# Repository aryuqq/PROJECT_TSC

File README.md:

# InkTime v6 - Advanced Open Source Smartwatch

InkTime v6 este un smartwatch open-source de inalta performanta, axat pe eficienta energetica extrema si un factor de forma compact. Aceasta revizie hardware aduce imbunatatiri majore pe partea de management al energiei, feedback haptic avansat si generarea tensiunilor pentru display direct pe placa de baza.

Acest repository contine fisierele de design hardware (Schematice, PCB layout, BOM) pentru faza **EVT (Engineering Validation Test)** a versiunii 6.

## 1. Diagrama Bloc a Sistemului

```mermaid
graph TD
    %% Power Management
    USB[Conector USB-C / ESD] -->|5V| CHG[IC Incarcare BQ25180]
    CHG --> BATT[Acumulator LiPo 3.7V]
    BATT --> FG[Fuel Gauge MAX17048]
    BATT --> DCDC[Buck-Boost RT6160]
    
    %% Core Power
    DCDC -.->|3.3V Stabilizat| MCU[SoC nRF52840]
    DCDC -.->|3.3V| PERIPH[Periferice]
    
    %% Core & Connectivity
    MCU <-->|I2C| FG
    
    %% Interfaces & Peripherals
    MCU <-->|SPI + Control| EINK[Display E-Paper 1.54]
    MCU -->|PWM/Control| EINK_DRV[Circuit E-Paper Drive On-Board]
    MCU <-->|I2C + INT| IMU[Accelerometru BMA423]
    MCU <-->|I2C + EN| HAPTIC[Driver Haptic DRV2605]
    HAPTIC --> VIB[Motor LRA/ERM]
    MCU -->|GPIO| BTN[3x Butoane Navigare]
```

## 2. Bill Of Materials (BOM)

Tabelul de mai jos contine circuitele integrate (IC-urile) principale folosite in designul placii. Lista completa se gaseste in fisierul .csv din folderul Manufacturing.
| Componenta | Rol in sistem | JLC Part # | Link Datasheet |
| :--- | :--- | :--- | :--- |
| **nRF52840-QIAA** | Microcontroller principal (BLE, Cortex-M4F) | C206001 | [Datasheet nRF52840](https://infocenter.nordicsemi.com/pdf/nRF52840_PS_v1.7.pdf) |
| **BQ25180YBGR** | IC Incarcare liniara avansata (Ultra-Low Iq) | N/A | [Datasheet BQ25180](https://www.ti.com/lit/ds/symlink/bq25180.pdf) |
| **RT6160AWSC** | Regulator DC/DC Buck-Boost 3.3V | C2836254 | [Datasheet RT6160](https://www.richtek.com/assets/product_file/RT6160A/DS6160A-02.pdf) |
| **MAX17048G+T10** | Fuel Gauge (Monitorizare Baterie prin I2C) | C113374 | [Datasheet MAX17048](https://www.analog.com/media/en/technical-documentation/data-sheets/MAX17048-MAX17049.pdf) |
| **BMA423** | Accelerometru Ultra-Low Power (Pedometer HW) | C283084 | [Datasheet BMA423](https://www.bosch-sensortec.com/media/boschsensortec/downloads/datasheets/bst-bma423-ds004.pdf) |
| **DRV2605YZFR** | Driver Haptic I2C (Generare vibratii complexe) | C63435 | [Datasheet DRV2605](https://www.ti.com/lit/ds/symlink/drv2605.pdf) |
| **USBLC6-2SC6Y** | Protectie ESD pe liniile de date si alimentare USB-C | C7519 | [Datasheet USBLC6](https://www.st.com/resource/en/datasheet/usblc6-2.pdf) |

## 3. Descrierea Functionalitatii Hardware
### Procesare si Conectivitate:

Inima ceasului InkTime este SoC-ul Nordic nRF52840. A fost ales datorita suportului nativ pentru Bluetooth 5.0 (BLE), esential pentru sincronizarea notificarilor cu telefonul mobil. Arhitectura ARM Cortex-M4F permite procesarea eficienta a algoritmilor senzorilor.
Managementul Consumului de Energie (Power Tree):

Fiind un dispozitiv wearable, constrangerile de baterie sunt critice. Sistemul energetic a fost complet reproiectat in v6.

Sistemul este alimentat de o baterie LiPo de mici dimensiuni (ex. 500mAh). Monitorizarea starii de incarcare (SoC) se face precis si fara consum mare de curent prin cipul MAX17048.

Incarcarea se face la 5V printr-un circuit BQ25180, un cip de top care permite controlul precis al pragurilor de incarcare.

Pentru a asigura tensiunea de 3.3V am folosit un convertor Buck-Boost RT6160 in loc de un LDO simplu. Acesta mentine 3.3V perfect stabil chiar si cand tensiunea bateriei scade, extragand maximum de energie din acumulator inainte de oprire.

### Periferice si Interfete:

Display-ul E-Ink: Comunica prin protocol SPI. Fata de versiunile anterioare, placa include propriul circuit de generare a tensiunilor inalte (E-Paper Drive On-Board cu inductor si mosfet), ceea ce reduce grosimea totala. Consuma 0mA pentru a mentine imaginea afisata.

Senzorii (IMU, Haptic, Fuel Gauge): Comunicatia se realizeaza pe o magistrala I2C partajata. BMA423 are un mod special de "step counter" hardware care poate trezi microcontroller-ul din sleep doar cand utilizatorul face un pas. Driver-ul DRV2605 ofera feedback haptic premium, descarcand procesorul de generarea semnalelor PWM.

## 4. Alocarea Pinilor nRF52840

Microcontroller-ul nRF52840 permite maparea flexibila a pinilor (orice functie digitala pe orice pin), lucru care a facilitat o rutare curata pe PCB.

| Pin nRF52840 | Nume Net / Functie | Justificare / Detalii |
| :--- | :--- | :--- |
| **P0.26 / P0.27** | `SDA/2.4C`, `SCL/2.4C` | Magistrala I2C principala (IMU, Haptic, Fuel Gauge, Charger). Contine rezistente de pull-up. |
| **P0.08 / P1.09** | `IMU_INT1`, `IMU_INT2` | Pini de intrerupere hardware. BMA423 trimite semnale aici pentru a trezi SoC-ul cand detecteaza miscare. |
| **P0.12** | `HAPTIC_EN` | Pin configurat ca iesire pentru a activa/dezactiva driver-ul de vibratii DRV2605. |
| **P0.04** | `EPD_CS` | Chip Select pentru activarea magistralei SPI a display-ului E-Paper. |
| **P0.13 - P0.15** | `MOSI`, `MISO`, `SCK` | Magistrala SPI hardware (rutata direct catre conectorul FPC de 24 pini). |
| **Diverse** | `SW_UP`, `SW_ENT`, `SW_DN` | Pini conectati la butoanele laterale, configurati cu retele RC (Hardware Debouncing) pentru o citire curata. |

## 5. Design Log & Integrare Mecanica
### Constructia PCB-ului:

Layout-ul este extrem de dens, folosind componente in capsule miniaturale (BGA si QFN). Rutarea respecta zona de "Keepout" a antenei de 2.4GHz, asigurand o bataie maxima a semnalului Bluetooth.
Interfete Fizice:

Conectorul USB Type-C este utilizat exclusiv pentru incarcare (5V) si a fost ranforsat mecanic. Debug-ul se face prin footprint-ul SWD standardizat (Tag-Connect TC2030).

## 6. Calcule Detaliate de Consum de Energie (Power Budget)

Dispozitivul este proiectat sa functioneze cu un acumulator LiPo de 500 mAh.
### Consum in Mod Sleep (Standby / System OFF)

    * nRF52840 (Sleep): ~1.5 uA

    * BMA423 (Low Power): ~2.0 uA

    * MAX17048 (Hibernate): ~0.5 uA

    * BQ25180 (Battery Discharge): ~10.0 uA

    * RT6160 (Quiescent): ~1.0 uA

    * Total Consum Sleep: ~15.0 uA (0.015 mA)

### Consum in Mod Activ (Actualizare Ecran / Bluetooth)

    * nRF52840 (CPU + TX RF): ~14.0 mA

    * E-Paper Drive (in timpul refresh-ului): ~8.0 mA

    * Total Consum Activ (varf): ~22.0 mA

### Estimarea Autonomiei

Presupunand un ciclu de utilizare cu 50 de treziri pe zi si o medie calculata de 0.15 mA consum hibrid:

500 mAh / 0.15 mA = 3333 ore = Aproximativ 138 de zile (peste 4 luni) teoretice cu o singura incarcare.

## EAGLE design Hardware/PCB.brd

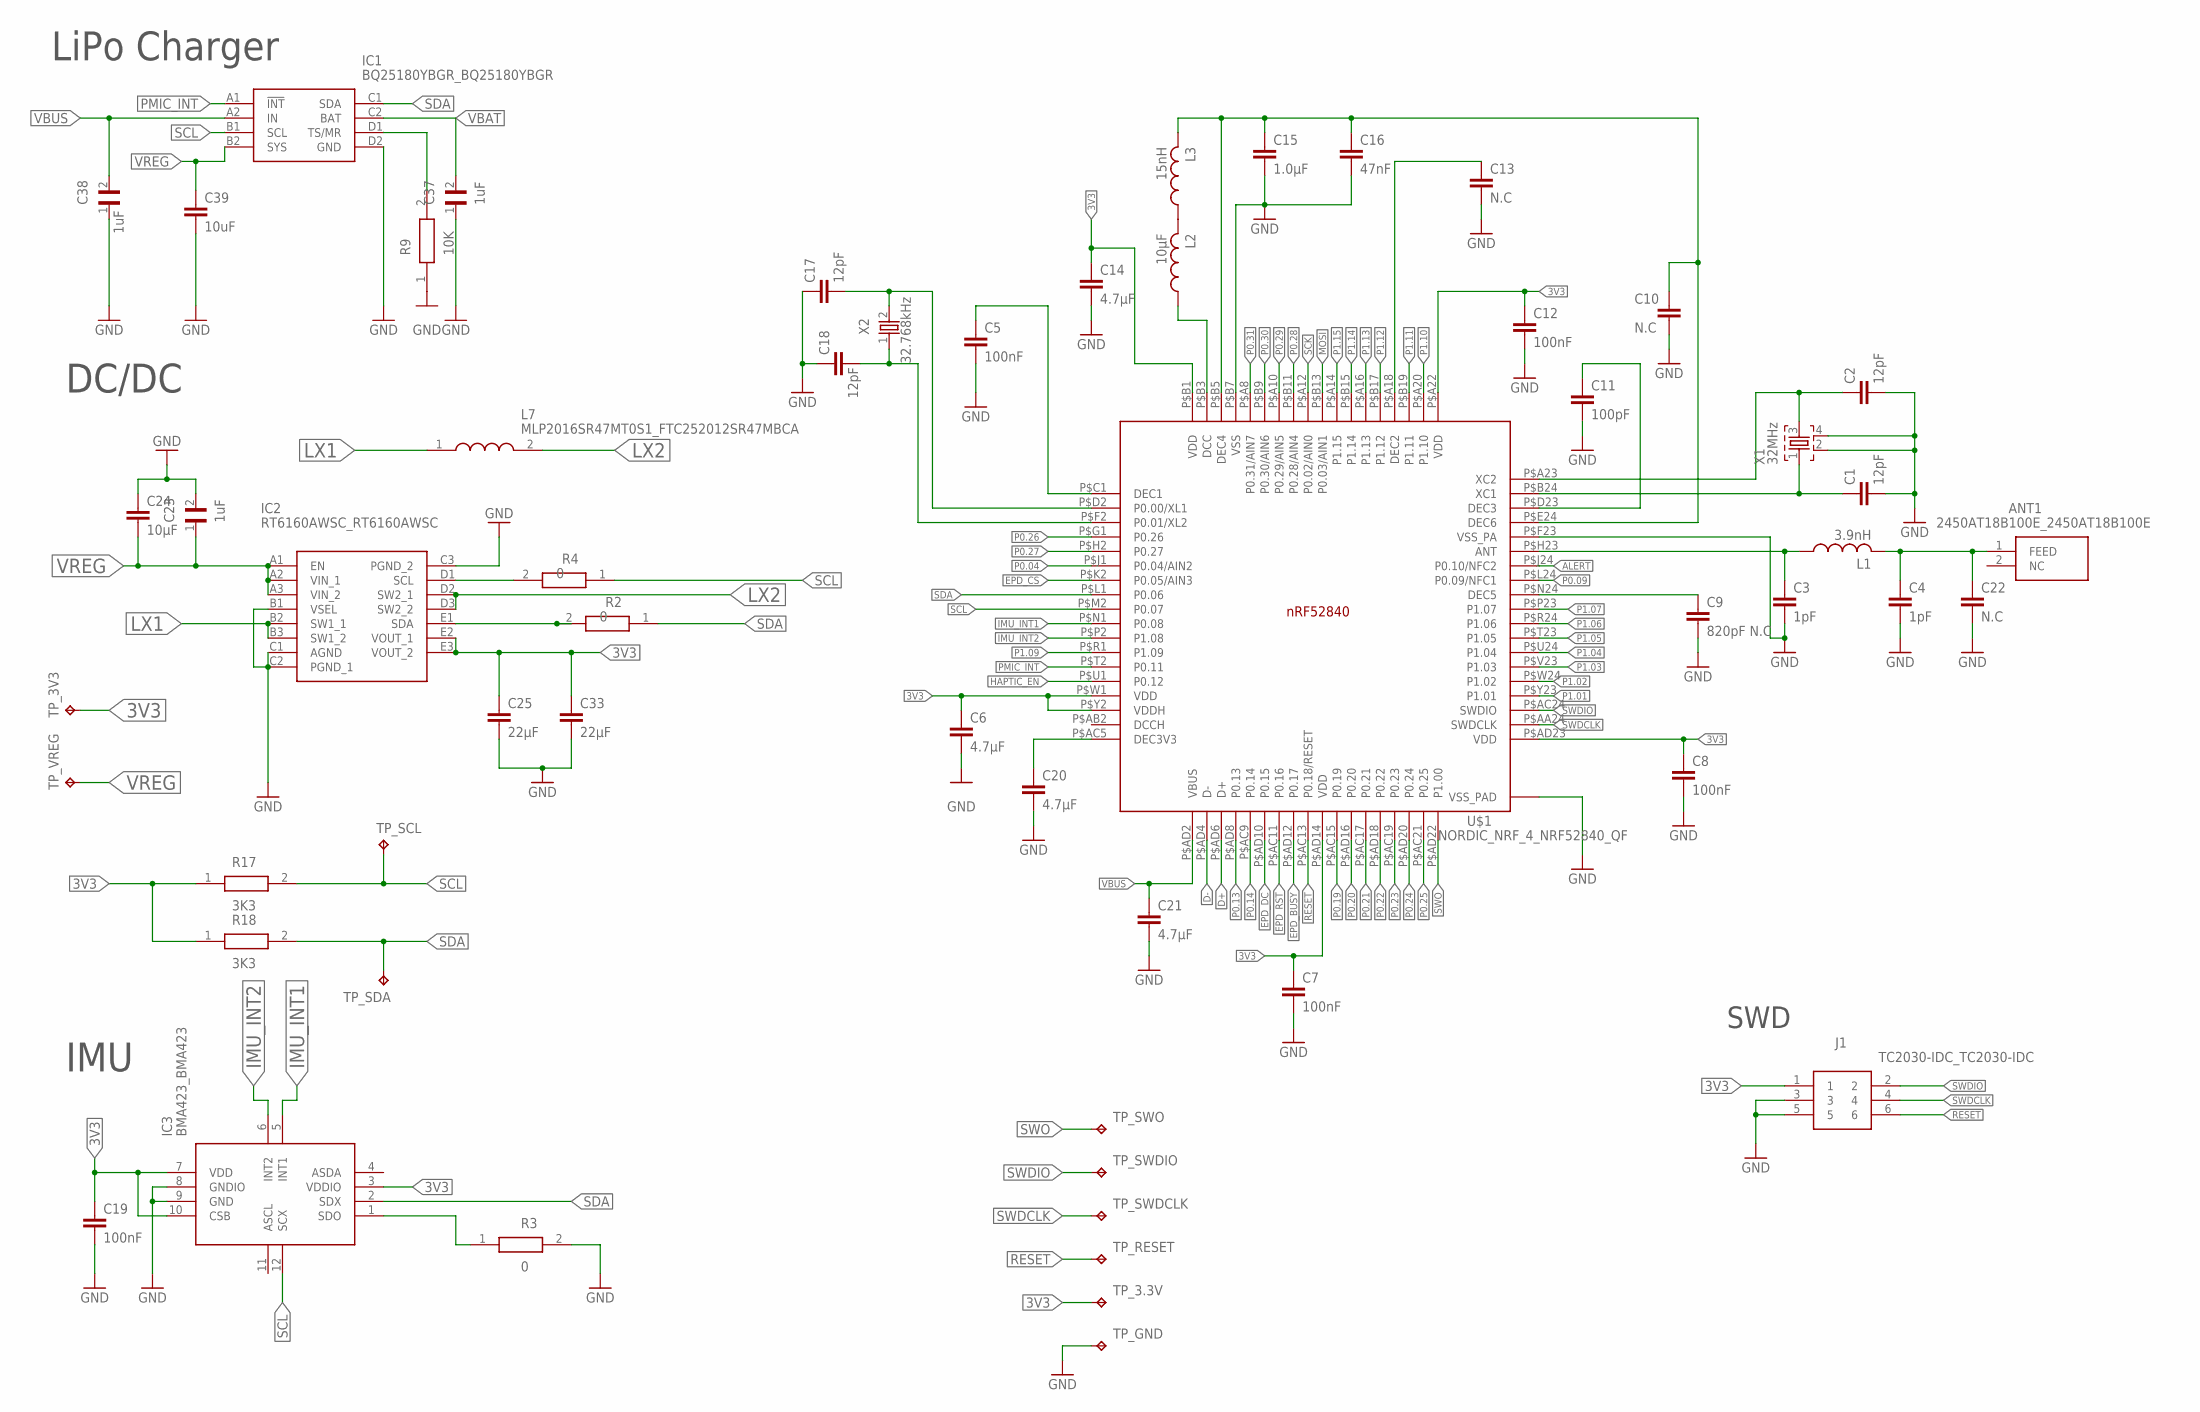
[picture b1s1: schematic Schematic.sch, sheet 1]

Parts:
ANT1: 2450AT18B100E_2450AT18B100E; 2450AT18B100E_ANTC3216X140N
C1, C2, C17, C18: 12pF; NORDIC_NRF_3_RESC0201_L
C3, C4: 1pF; NORDIC_NRF_3_RESC0201_L
C5, C7, C8, C12, C19: 100nF; NORDIC_NRF_3_RESC0201_L
C6, C14, C20, C21: 4.7µF; PERFECT_0402_0402
C9: 820pF N.C; NORDIC_NRF_3_RESC0201_L
C10: N.C; PERFECT_0402_0402
C11: 100pF; NORDIC_NRF_3_RESC0201_L
C13, C22: N.C; NORDIC_NRF_3_RESC0201_L
C15: 1.0µF; PERFECT_0402_0402
C16: 47nF; NORDIC_NRF_3_RESC0201_L
C23, C37, C38: 1uF; GRM011R60J152KE01L_2_CAPC0201X13N
C24: 10µF; PERFECT_0402_0402
C25, C33: 22µF; PERFECT_0402_0402
C39: 10uF; PERFECT_0402_0402
IC1: BQ25180YBGR_BQ25180YBGR; BQ25180YBGR_BGA8C40P2X4_100X155X50
IC2: RT6160AWSC_RT6160AWSC; RT6160AWSC_BGA15C40P3X5_140X230X60
IC3: BMA423_BMA423
J1: TC2030-IDC_TC2030-IDC; TC2030-IDC_TC2030IDC
L1: 3.9nH; NORDIC_NRF_2_RESC0402_L
L2: 10µF; NORDIC_NRF_2_RESC0402_L
L3: 15nH; NORDIC_NRF_2_RESC0402_L
L7: MLP2016SR47MT0S1_FTC252012SR47MBCA; MLP2016SR47MT0S1_INDC2016X100N
R2, R3, R4: 0; CPF0201D7K68C1_0201
R9: 10K; CPF0201D7K68C1_0201
R17, R18: 3K3; ERA-1AEB3401C_0201
TP_3.3V, TP_3V3: HECTOR_WATCH_1_TPTP20R; HECTOR_WATCH_1_TP20R
TP_GND: HECTOR_WATCH_1_TPTP20R; HECTOR_WATCH_1_TP20R
TP_RESET: HECTOR_WATCH_1_TPTP20R; HECTOR_WATCH_1_TP20R
TP_SCL: HECTOR_WATCH_1_TPTP20R; HECTOR_WATCH_1_TP20R
TP_SDA: HECTOR_WATCH_1_TPTP20R; HECTOR_WATCH_1_TP20R
TP_SWDCLK: HECTOR_WATCH_1_TPTP20R; HECTOR_WATCH_1_TP20R
TP_SWDIO: HECTOR_WATCH_1_TPTP20R; HECTOR_WATCH_1_TP20R
TP_SWO: HECTOR_WATCH_1_TPTP20R; HECTOR_WATCH_1_TP20R
TP_VREG: HECTOR_WATCH_1_TPTP20R; HECTOR_WATCH_1_TP20R
U$1: NORDIC_NRF_4_NRF52840_QF; NORDIC_NRF_4_AQFN50P700X700X85_HS-74N
X1: 32MHz; NORDIC_NRF_BT-XTAL_2016_N
X2: 32.768kHz; NORDIC_NRF_1_XTAL_3215_N

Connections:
3V3: C6.1, C7.1, C8.1, C12.1, C14.1, C19.1, C25.1, C33.1, IC2.E2 (VOUT_1), IC2.E3 (VOUT_2), IC3.3 (VDDIO), IC3.7 (VDD), IC3.10 (CSB), J1.1, R17.1, R18.1, TP_3.3V.TP, TP_3V3.TP, U$1.P$A22 (VDD), U$1.P$AD14 (VDD), U$1.P$AD23 (VDD), U$1.P$B1 (VDD), U$1.P$W1 (VDD), U$1.P$Y2 (VDDH); also elsewhere on the board
ALERT: U$1.P$J24 (P0.10/NFC2); also elsewhere on the board
D+: U$1.P$AD6 (D+); also elsewhere on the board
D-: U$1.P$AD4 (D-); also elsewhere on the board
EPD_BUSY: U$1.P$AD12 (P0.17); also elsewhere on the board
EPD_CS: U$1.P$K2 (P0.05/AIN3); also elsewhere on the board
EPD_DC: U$1.P$AD10 (P0.15); also elsewhere on the board
EPD_RST: U$1.P$AC11 (P0.16); also elsewhere on the board
GND: C1.2, C2.2, C3.2, C4.2, C5.2, C6.2, C7.2, C8.2, C9.2, C10.2, C11.2, C12.2, C13.2, C14.2, C15.2, C16.2, C17.1, C18.1, C19.2, C20.2, C21.2, C22.2, C23.2, C24.1, C25.2, C33.2, C37.1, C38.1, C39.2, IC1.D2 (GND), IC2.B1 (VSEL), IC2.C1 (AGND), IC2.C2 (PGND_1), IC2.C3 (PGND_2), IC3.8 (GNDIO), IC3.9 (GND), J1.3, J1.5, R3.2, R9.1, TP_GND.TP, U$1.P$74 (VSS_PAD), U$1.P$75 (VSS_PAD), U$1.P$76 (VSS_PAD), U$1.P$77 (VSS_PAD), U$1.P$78 (VSS_PAD), U$1.P$79 (VSS_PAD), U$1.P$80 (VSS_PAD), U$1.P$81 (VSS_PAD), U$1.P$82 (VSS_PAD), U$1.P$83 (VSS_PAD), U$1.P$84 (VSS_PAD), U$1.P$85 (VSS_PAD), U$1.P$86 (VSS_PAD), U$1.P$87 (VSS_PAD), U$1.P$88 (VSS_PAD), U$1.P$89 (VSS_PAD), U$1.P$90 (VSS_PAD), U$1.P$B7 (VSS), U$1.P$F23 (VSS_PA), X1.2, X1.4; also elsewhere on the board
HAPTIC_EN: U$1.P$U1 (P0.12); also elsewhere on the board
IMU_INT1: IC3.5 (INT1), U$1.P$N1 (P0.08)
IMU_INT2: IC3.6 (INT2), U$1.P$P2 (P1.08)
LX1: IC2.B2 (SW1_1), IC2.B3 (SW1_2), L7.1
LX2: IC2.D2 (SW2_1), IC2.D3 (SW2_2), L7.2
MOSI: U$1.P$B13 (P0.03/AIN1); also elsewhere on the board
unnamed: L2.2, L3.1
unnamed: L2.1, U$1.P$B3 (DCC)
unnamed: IC1.D1 (TS/MR), R9.2
unnamed: IC3.1 (SDO), R3.1
unnamed: IC2.D1 (SCL), R4.2
unnamed: C10.1, C15.1, C16.1, L3.2, U$1.P$B5 (DEC4), U$1.P$E24 (DEC6)
unnamed: IC2.E1 (SDA), R2.2
unnamed: C13.1, U$1.P$A18 (DEC2)
unnamed: C11.1, U$1.P$D23 (DEC3)
unnamed: C2.1, U$1.P$A23 (XC2), X1.3
unnamed: C1.1, U$1.P$B24 (XC1), X1.1
unnamed: C3.1, L1.1, U$1.P$H23 (ANT)
unnamed: ANT1.1 (FEED), C4.1, C22.1, L1.2
unnamed: C9.1, U$1.P$N24 (DEC5)
unnamed: C20.1, U$1.P$AC5 (DEC3V3)
unnamed: C5.1, U$1.P$C1 (DEC1)
unnamed: C17.2, U$1.P$D2 (P0.00/XL1), X2.2
unnamed: C18.2, U$1.P$F2 (P0.01/XL2), X2.1
P0.04: U$1.P$J1 (P0.04/AIN2)
P0.09: U$1.P$L24 (P0.09/NFC1)
P0.13: U$1.P$AD8 (P0.13); also elsewhere on the board
P0.14: U$1.P$AC9 (P0.14); also elsewhere on the board
P0.19: U$1.P$AC15 (P0.19)
P0.20: U$1.P$AD16 (P0.20)
P0.21: U$1.P$AC17 (P0.21)
P0.22: U$1.P$AD18 (P0.22)
P0.23: U$1.P$AC19 (P0.23)
P0.24: U$1.P$AD20 (P0.24)
P0.25: U$1.P$AC21 (P0.25)
P0.26: U$1.P$G1 (P0.26)
P0.27: U$1.P$H2 (P0.27)
P0.28: U$1.P$B11 (P0.28/AIN4)
P0.29: U$1.P$A10 (P0.29/AIN5)
P0.30: U$1.P$B9 (P0.30/AIN6)
P0.31: U$1.P$A8 (P0.31/AIN7)
P1.01: U$1.P$Y23 (P1.01); also elsewhere on the board
P1.02: U$1.P$W24 (P1.02); also elsewhere on the board
P1.03: U$1.P$V23 (P1.03)
P1.04: U$1.P$U24 (P1.04)
P1.05: U$1.P$T23 (P1.05)
P1.06: U$1.P$R24 (P1.06)
P1.07: U$1.P$P23 (P1.07)
P1.09: U$1.P$R1 (P1.09)
P1.10: U$1.P$A20 (P1.10)
P1.11: U$1.P$B19 (P1.11)
P1.12: U$1.P$B17 (P1.12)
P1.13: U$1.P$A16 (P1.13)
P1.14: U$1.P$B15 (P1.14)
P1.15: U$1.P$A14 (P1.15)
PMIC_INT: IC1.A1 (!INT), U$1.P$T2 (P0.11)
RESET: J1.6, TP_RESET.TP, U$1.P$AC13 (P0.18/RESET)
SCK: U$1.P$A12 (P0.02/AIN0); also elsewhere on the board
SCL: IC1.B1 (SCL), IC3.12 (SCX), R4.1, R17.2, TP_SCL.TP, U$1.P$M2 (P0.07); also elsewhere on the board
SDA: IC1.C1 (SDA), IC3.2 (SDX), R2.1, R18.2, TP_SDA.TP, U$1.P$L1 (P0.06); also elsewhere on the board
SWDCLK: J1.4, TP_SWDCLK.TP, U$1.P$AA24 (SWDCLK)
SWDIO: J1.2, TP_SWDIO.TP, U$1.P$AC24 (SWDIO)
SWO: TP_SWO.TP, U$1.P$AD22 (P1.00)
VBAT: C37.2, IC1.C2 (BAT); also elsewhere on the board
VBUS: C21.1, C38.2, IC1.A2 (IN), U$1.P$AD2 (VBUS); also elsewhere on the board
VREG: C23.1, C24.2, C39.1, IC1.B2 (SYS), IC2.A1 (EN), IC2.A2 (VIN_1), IC2.A3 (VIN_2), TP_VREG.TP

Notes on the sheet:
LiPo Charger
DC/DC
IMU
SWD

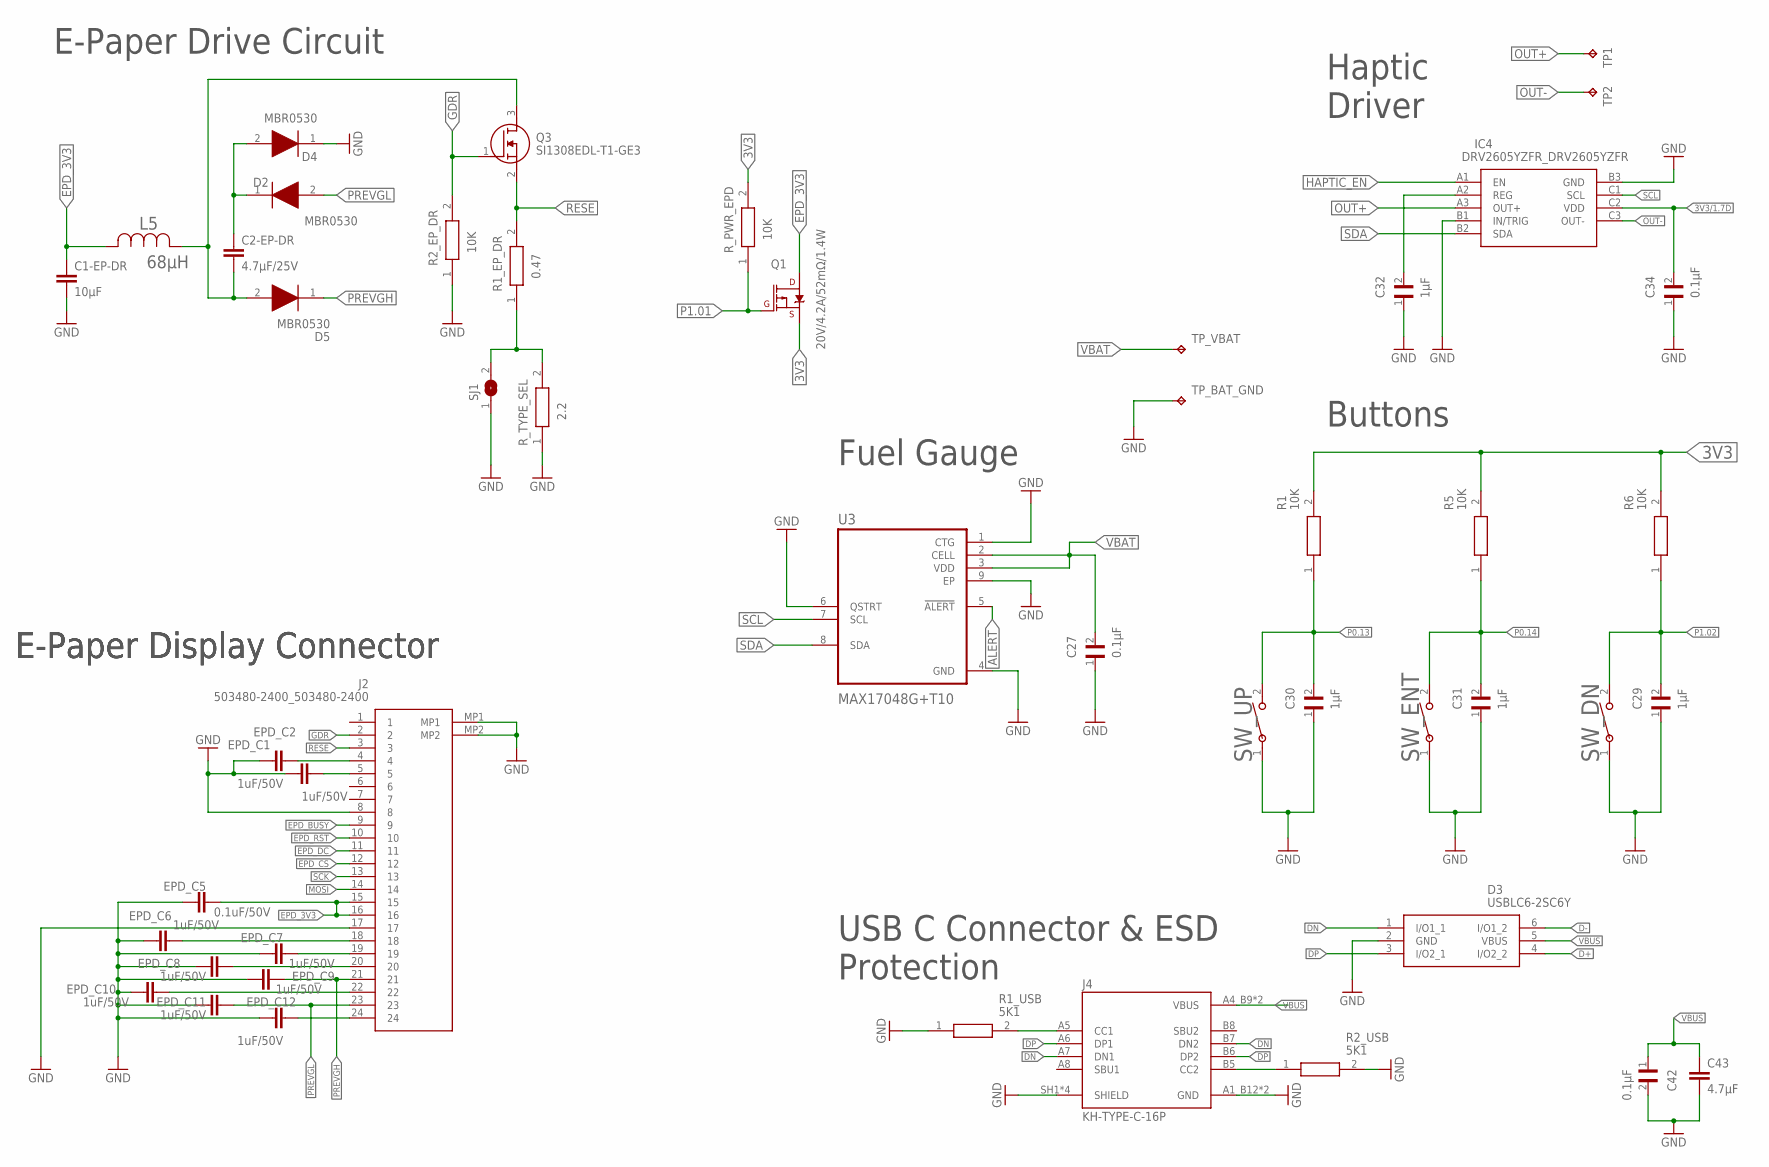
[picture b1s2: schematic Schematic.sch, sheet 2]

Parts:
C1-EP-DR: 10µF; NORDIC_NRF_3_RESC0402_L
C2-EP-DR: 4.7µF/25V; NORDIC_NRF_3_RESC0603_L
C27, C42: 0.1µF; GRM011R60J152KE01L_1_0201
C29, C30, C31, C32: 1µF; GRM011R60J152KE01L_1_0201
C34: 0.1µF; GRM011R60J152KE01L_2_CAPC0201X13N
C43: 4.7µF; PERFECT_0402_0402
D2, D4, D5: MBR0530; ESP32_C6_LIBRARY_5_SOD3716X135N
D3: USBLC6-2SC6Y; ESP32_C6_LIBRARY_3_SOT95P280X145-6N
EPD_C1, EPD_C2, EPD_C6, EPD_C7, EPD_C8, EPD_C9, EPD_C10, EPD_C11, EPD_C12: 1uF/50V; PERFECT_0402_0402
EPD_C5: 0.1uF/50V; NORDIC_NRF_3_RESC0201_L
IC4: DRV2605YZFR_DRV2605YZFR; DRV2605YZFR_BGA9C50P3X3_144X144X62
J2: 503480-2400_503480-2400; 503480-2400_5034802400
J4: KH-TYPE-C-16P; KH-TYPE-C-16P_KINGHELM_KH-TYPE-C-16P
L5: 68µH; ESP32_C6_LIBRARY_2_IND_4828-WE-TPC_WRE
Q1: 20V/4.2A/52mΩ/1.4W; ESP32_C6_LIBRARY_4_ESP32_C6_LIBRARY_4_ESP32_C6_LIBRARY_4_ES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
Q3: SI1308EDL-T1-GE3; ESP32_C6_LIBRARY_6_SOT65P210X110-3N
R1, R2_EP_DR, R5, R6: 10K; CPF0201D7K68C1_0201
R1_EP_DR: 0.47; CPF0201D7K68C1_0201
R1_USB, R2_USB: 5K1; CPF0201D7K68C1_0201
R_PWR_EPD: 10K; CPF0201D7K68C1_0201
R_TYPE_SEL: 2.2; CPF0201D7K68C1_0201
SJ1: ESP32_C6_LIBRARY_7_JUMPER_SJ
SW_DN: 2025-10-22_07-23-44_LIBRARY_EVP-AKE31ASW_EVP-AKE3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; 2025-10-22_07-23-44_LIBRARY_SW_EVP-AKE31A_PAN
SW_ENT: 2025-10-22_07-23-44_LIBRARY_EVP-AKE31ASW_EVP-AKE3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; 2025-10-22_07-23-44_LIBRARY_SW_EVP-AKE31A_PAN
SW_UP: 2025-10-22_07-23-44_LIBRARY_EVP-AKE31ASW_EVP-AKE3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; 2025-10-22_07-23-44_LIBRARY_SW_EVP-AKE31A_PAN
TP1, TP2: HECTOR_WATCH_1_TPTP20R; HECTOR_WATCH_1_TP20R
TP_BAT_GND: HECTOR_WATCH_1_TPTP20R; HECTOR_WATCH_1_TP20R
TP_VBAT: HECTOR_WATCH_1_TPTP20R; HECTOR_WATCH_1_TP20R
U3: MAX17048G+T10; ESP32_C6_LIBRARY_SON50P200X200X80-9N

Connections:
3V3: Q1.2 (S), R1.2, R5.2, R6.2, R_PWR_EPD.2; also elsewhere on the board
3V3/1.7D: C34.2, IC4.C2 (VDD)
ALERT: U3.5 (!ALERT); also elsewhere on the board
D+: D3.4 (I/O2_2); also elsewhere on the board
D-: D3.6 (I/O1_2); also elsewhere on the board
DN: D3.1 (I/O1_1), J4.A7 (DN1), J4.B7 (DN2)
DP: D3.3 (I/O2_1), J4.A6 (DP1), J4.B6 (DP2)
EPD_3V3: C1-EP-DR.1, EPD_C5.2, J2.15, J2.16, L5.2, Q1.3 (D)
EPD_BUSY: J2.9; also elsewhere on the board
EPD_CS: J2.12; also elsewhere on the board
EPD_DC: J2.11; also elsewhere on the board
EPD_RST: J2.10; also elsewhere on the board
GDR: J2.2, Q3.1 (G), R2_EP_DR.2
GND: C1-EP-DR.2, C27.1, C29.1, C30.1, C31.1, C32.1, C34.1, C42.2, C43.2, D3.2 (GND), D4.1 (K), EPD_C1.1, EPD_C2.1, EPD_C5.1, EPD_C6.1, EPD_C7.1, EPD_C8.1, EPD_C9.1, EPD_C10.1, EPD_C11.1, EPD_C12.1, IC4.B1 (IN/TRIG), IC4.B3 (GND), J2.8, J2.17, J2.MP1, J2.MP2, J4.A1_B12 (GND), J4.A12_B1 (GND), J4.SH1 (SHIELD), J4.SH2 (SHIELD), J4.SH3 (SHIELD), J4.SH4 (SHIELD), R1_USB.1, R2_EP_DR.1, R2_USB.2, R_TYPE_SEL.1, SJ1.1, SW_DN.1, SW_ENT.1, SW_UP.1, TP_BAT_GND.TP, U3.1 (CTG), U3.4 (GND), U3.6 (QSTRT), U3.9 (EP); also elsewhere on the board
HAPTIC_EN: IC4.A1 (EN); also elsewhere on the board
MOSI: J2.14; also elsewhere on the board
unnamed: EPD_C1.2, J2.5
unnamed: C2-EP-DR.2, D5.2 (A), L5.1, Q3.3 (D)
unnamed: EPD_C2.2, J2.4
unnamed: C32.2, IC4.A2 (REG)
unnamed: C2-EP-DR.1, D2.1 (K), D4.2 (A)
unnamed: J4.B5 (CC2), R2_USB.1
unnamed: J4.A5 (CC1), R1_USB.2
unnamed: R1_EP_DR.1, R_TYPE_SEL.2, SJ1.2
unnamed: EPD_C6.2, J2.18
unnamed: EPD_C7.2, J2.19
unnamed: EPD_C8.2, J2.20
unnamed: EPD_C10.2, J2.22
unnamed: EPD_C12.2, J2.24
OUT+: IC4.A3 (OUT+), TP1.TP
OUT-: IC4.C3 (OUT-), TP2.TP
P0.13: C30.2, R1.1, SW_UP.2; also elsewhere on the board
P0.14: C31.2, R5.1, SW_ENT.2; also elsewhere on the board
P1.01: Q1.1 (G), R_PWR_EPD.1; also elsewhere on the board
P1.02: C29.2, R6.1, SW_DN.2; also elsewhere on the board
PREVGH: D5.1 (K), EPD_C9.2, J2.21
PREVGL: D2.2 (A), EPD_C11.2, J2.23
RESE: J2.3, Q3.2 (S), R1_EP_DR.2
SCK: J2.13; also elsewhere on the board
SCL: IC4.C1 (SCL), U3.7 (SCL); also elsewhere on the board
SDA: IC4.B2 (SDA), U3.8 (SDA); also elsewhere on the board
VBAT: C27.2, TP_VBAT.TP, U3.2 (CELL), U3.3 (VDD); also elsewhere on the board
VBUS: C42.1, C43.1, D3.5 (VBUS), J4.A4_B9 (VBUS), J4.A9_B4 (VBUS); also elsewhere on the board

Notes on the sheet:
Haptic Driver
Fuel Gauge
Buttons
USB C Connector & ESD Protection
E-Paper Display Connector
E-Paper Drive Circuit

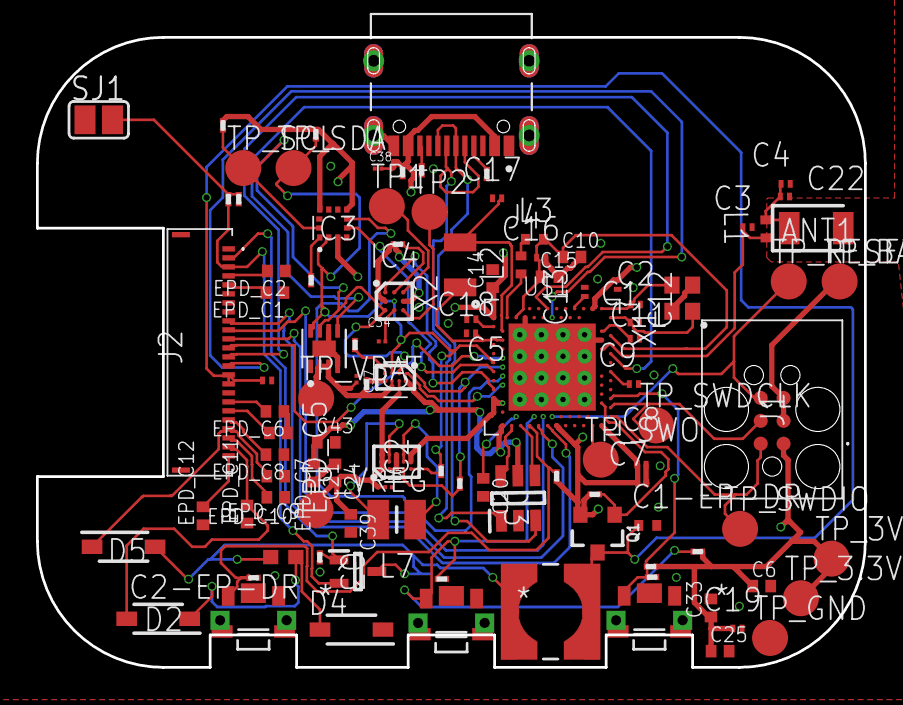
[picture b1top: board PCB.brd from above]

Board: 4 copper layers, 46.0 x 35.0 mm, 105 parts (0 on the bottom side), 71 nets.

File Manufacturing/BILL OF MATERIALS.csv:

Reference Designators;Quantity;Description;Package;Value;Manufacturer;Manufacturer Part Number;Vendor;Vendor Part Number;Top/Bottom;
;1;PCB Board;Board;;;;;;;
ANT1;1;Antennas 2.45GHz ANTENNA;2450AT18B100E_ANTC3216X140N;2450AT18B100E_2450AT18B100E;;;;;Top;
C1, C2, C17, C18;4;Generic chip capacitor;NORDIC_NRF_3_RESC0201_L;12pF;;;;;Top;
C1-EP-DR;1;Generic chip capacitor;NORDIC_NRF_3_RESC0402_L;10µF;;;;;Top;
C2-EP-DR;1;Generic chip capacitor;NORDIC_NRF_3_RESC0603_L;4.7µF/25V;;;;;Top;
C3, C4;2;Generic chip capacitor;NORDIC_NRF_3_RESC0201_L;1pF;;;;;Top;
C5, C7, C8, C12, C19;5;Generic chip capacitor;NORDIC_NRF_3_RESC0201_L;100nF;;;;;Top;
C6, C14, C20, C21, C43;5;0402 (1005 Metric);PERFECT_0402_0402;4.7µF;;;;;Top;
C9;1;Generic chip capacitor;NORDIC_NRF_3_RESC0201_L;820pF N.C;;;;;Top;
C10;1;0402 (1005 Metric);PERFECT_0402_0402;N.C;;;;;Top;
C11;1;Generic chip capacitor;NORDIC_NRF_3_RESC0201_L;100pF;;;;;Top;
C13, C22;2;Generic chip capacitor;NORDIC_NRF_3_RESC0201_L;N.C;;;;;Top;
C15;1;0402 (1005 Metric);PERFECT_0402_0402;1.0µF;;;;;Top;
C16;1;Generic chip capacitor;NORDIC_NRF_3_RESC0201_L;47nF;;;;;Top;
C23, C37, C38;3;Check availability;CAPC0201X13N;1uF;;;;;Top;
C24;1;0402 (1005 Metric);PERFECT_0402_0402;10µF;;;;;Top;
C25, C33;2;0402 (1005 Metric);PERFECT_0402_0402;22µF;;;;;Top;
C27, C42;2;Check availability;GRM011R60J152KE01L_1_0201;0.1µF;;;;;Top;
C29, C30, C31, C32;4;Check availability;GRM011R60J152KE01L_1_0201;1µF;;;;;Top;
C34;1;Check availability;CAPC0201X13N;0.1µF;;;;;Top;
C39;1;0402 (1005 Metric);PERFECT_0402_0402;10uF;;;;;Top;
D2, D4, D5;3;ON SEMICONDUCTOR - MBR0530 - DIODE, SCHOTTKY, 0.5A, 30V, SOD-123;SOD3716X135N;MBR0530;;;;;Top;
D3;1;Low Cap. ESD Protection Auto SOT-23-6 STMicroelectronics USBLC6-2SC6Y, Dual Uni-Directional TVS Diode Array, 6-Pin SOT-23;SOT95P280X145-6N;USBLC6-2SC6Y;;;;;Top;
EPD_C1, EPD_C2, EPD_C6, EPD_C7, EPD_C8, EPD_C9, EPD_C10, EPD_C11, EPD_C12;9;0402 (1005 Metric);PERFECT_0402_0402;1uF/50V;;;;;Top;
EPD_C5;1;Generic chip capacitor;NORDIC_NRF_3_RESC0201_L;0.1uF/50V;;;;;Top;
IC1;1;Charger IC Lithium Ion/Polymer, Lithium Iron Phosphate 8-DSBGA (1.6x1.1);BQ25180YBGR_BGA8C40P2X4_100X155X50;BQ25180YBGR_BQ25180YBGR;;;;;Top;
IC2;1;Buck-Boost Regulator Positive Output Step-Up/Step-Down I2C DC-DC Controller IC 15-WL-CSP (BSC) (1.4x2.3);RT6160AWSC_BGA15C40P3X5_140X230X60;RT6160AWSC_RT6160AWSC;;;;;Top;
IC3;1;Accelerometers Triaxial low-g 12bit Acceleration Sensor;BMA423_BMA423;BMA423_BMA423;;;;;Top;
IC4;1;Haptic Driver for ERM/LRA with Built-In Library and Smart Loop Architecture;DRV2605YZFR_BGA9C50P3X3_144X144X62;DRV2605YZFR_DRV2605YZFR;;;;;Top;
J1;1;CABLE ADAPTER 6 POS;TC2030-IDC_TC2030IDC;TC2030-IDC_TC2030-IDC;;;;;Top;
J2;1;FFC & FPC Connectors 0.5mm FPC RA SMT Dual Contact 24Ckt;503480-2400_5034802400;503480-2400_503480-2400;;;;;Top;
J4;1;Check availability;KINGHELM_KH-TYPE-C-16P;KH-TYPE-C-16P;;;;;Top;
L1;1;Generic chip inductor;NORDIC_NRF_2_RESC0402_L;3.9nH;;;;;Top;
L2;1;Generic chip inductor;NORDIC_NRF_2_RESC0402_L;10µF;;;;;Top;
L3;1;Generic chip inductor;NORDIC_NRF_2_RESC0402_L;15nH;;;;;Top;
L5;1;;ESP32_C6_LIBRARY_2_IND_4828-WE-TPC_WRE;68µH;;;;;Top;
L7;1;SMD / SMT Inductors (Coils), L=0.47?H, L x W x T :;MLP2016SR47MT0S1_INDC2016X100N;MLP2016SR47MT0S1_FTC252012SR47MBCA;;;;;Top;
Q1;1;P-channel MOSFETs;ESP32_WROVER_SPARKFUN-DISCRETESEMI_SOT23-3;20V/4.2A/52mΩ/1.4W;;;;;Top;
Q3;1;MOSFET N-Ch 30V 1.5A TrenchFET SC70 Vishay Si1308EDL-T1-GE3 N-channel MOSFET Transistor, 1.5 A, 30 V, 3-Pin SC-70;SOT65P210X110-3N;SI1308EDL-T1-GE3;;;;;Top;
R_PWR_EPD, R1, R2_EP_DR, R5, R6, R9;6;7.68k 0201 Thin Film Surface Mount Fixed Resistor +/-0.5% 0.031W CPF0201D7K68C1;CPF0201D7K68C1_0201;10K;;;;;Top;
R_TYPE_SEL;1;7.68k 0201 Thin Film Surface Mount Fixed Resistor +/-0.5% 0.031W CPF0201D7K68C1;CPF0201D7K68C1_0201;2.2;;;;;Top;
R1_EP_DR;1;7.68k 0201 Thin Film Surface Mount Fixed Resistor +/-0.5% 0.031W CPF0201D7K68C1;CPF0201D7K68C1_0201;0.47;;;;;Top;
R1_USB, R2_USB;2;7.68k 0201 Thin Film Surface Mount Fixed Resistor +/-0.5% 0.031W CPF0201D7K68C1;CPF0201D7K68C1_0201;5K1;;;;;Top;
R2, R3, R4;3;7.68k 0201 Thin Film Surface Mount Fixed Resistor +/-0.5% 0.031W CPF0201D7K68C1;CPF0201D7K68C1_0201;0;;;;;Top;
R17, R18;2;7.68k 0201 Thin Film Surface Mount Fixed Resistor +/-0.5% 0.031W CPF0201D7K68C1;R0201;3K3;;;;;Top;
SJ1;1;SMD solder JUMPER;JUMPER_SJ;;;;;;Top;
SW_DN, SW_ENT, SW_UP;3;;SW_EVP-AKE31A_PAN;2025-10-22_07-23-44_LIBRARY_EVP-AKE31ASW_EVP-AKE31A_PAN;;;;;Top;
TP_3.3V, TP_3V3, TP_BAT_GND, TP_GND, TP_RESET, TP_SCL, TP_SDA, TP_SWDCLK, TP_SWDIO, TP_SWO, TP_VBAT, TP_VREG, TP1, TP2;14;Test pad;HECTOR_WATCH_1_TP20R;HECTOR_WATCH_1_TPTP20R;;;;;Top;
U$1;1;nRF52840;NORDIC_NRF_4_AQFN50P700X700X85_HS-74N;NORDIC_NRF_4_NRF52840_QF;;;;;Top;
U3;1;Check availability;SON50P200X200X80-9N;MAX17048G+T10;;;;;Top;
X1;1;;NORDIC_NRF_BT-XTAL_2016_N;32MHz;;;;;Top;
X2;1;;NORDIC_NRF_1_XTAL_3215_N;32.768kHz;;;;;Top;

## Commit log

2026-04-10 Project
2026-04-10 Update README with project overview and specifications
    Added detailed project description and hardware functionality for smart clock.
2026-04-10 README with project details
    Added notes about component modifications and wire thickness adjustments to avoid overlaps.
2026-04-17 Added new updates
2026-04-22 README with project details
    Updated the README to include detailed information about the InkTime v6 smartwatch, including hardware functionality, power management, and component specifications.

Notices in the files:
parts and their libraries:
COPYRIGHT: Copyright (C) 2024 Ultra Librarian. All rights reserved.
COPYRIGHT: Copyright (C) 2025 Ultra Librarian. All rights reserved.
